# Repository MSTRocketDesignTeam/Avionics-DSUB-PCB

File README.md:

# Avionics-DSUB-PCB
Avionics DSUB board

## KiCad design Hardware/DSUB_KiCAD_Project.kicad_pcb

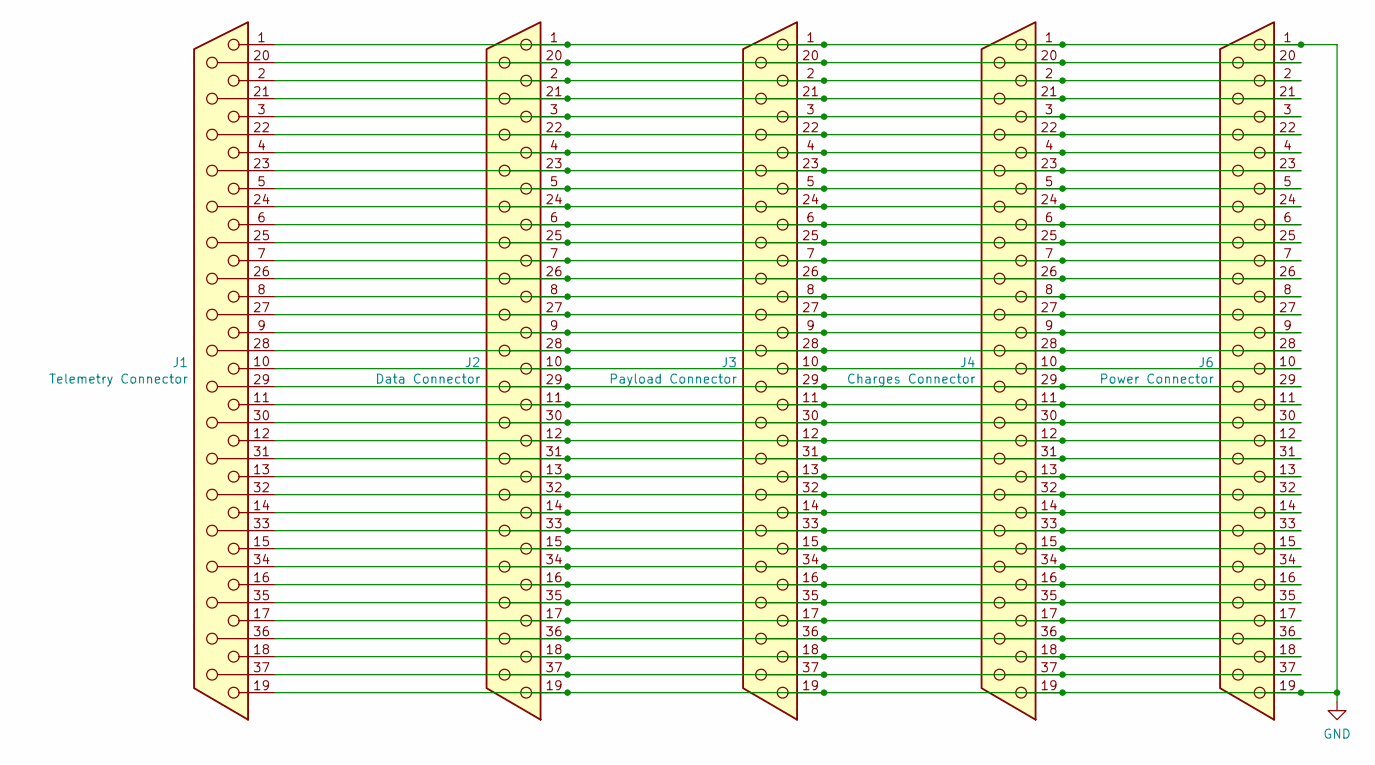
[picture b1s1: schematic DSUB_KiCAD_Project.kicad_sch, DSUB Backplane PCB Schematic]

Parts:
J1: Telemetry Connector; TE_1-747301-6
J2: Data Connector; TE_1-747301-6
J3: Payload Connector; TE_1-747301-6
J4: Charges Connector; TE_1-747301-6
J6: Power Connector; TE_1-747301-6

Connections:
GND: J1.1, J1.19, J2.1, J2.19, J3.1, J3.19, J4.1, J4.19, J6.1, J6.19
unnamed: J1.2, J2.2, J3.2, J4.2, J6.2
unnamed: J1.3, J2.3, J3.3, J4.3, J6.3
unnamed: J1.4, J2.4, J3.4, J4.4, J6.4
unnamed: J1.5, J2.5, J3.5, J4.5, J6.5
unnamed: J1.6, J2.6, J3.6, J4.6, J6.6
unnamed: J1.7, J2.7, J3.7, J4.7, J6.7
unnamed: J1.8, J2.8, J3.8, J4.8, J6.8
unnamed: J1.9, J2.9, J3.9, J4.9, J6.9
unnamed: J1.10, J2.10, J3.10, J4.10, J6.10
unnamed: J1.11, J2.11, J3.11, J4.11, J6.11
unnamed: J1.12, J2.12, J3.12, J4.12, J6.12
unnamed: J1.13, J2.13, J3.13, J4.13, J6.13
unnamed: J1.14, J2.14, J3.14, J4.14, J6.14
unnamed: J1.15, J2.15, J3.15, J4.15, J6.15
unnamed: J1.16, J2.16, J3.16, J4.16, J6.16
unnamed: J1.17, J2.17, J3.17, J4.17, J6.17
unnamed: J1.18, J2.18, J3.18, J4.18, J6.18
unnamed: J1.20, J2.20, J3.20, J4.20, J6.20
unnamed: J1.21, J2.21, J3.21, J4.21, J6.21
unnamed: J1.22, J2.22, J3.22, J4.22, J6.22
unnamed: J1.23, J2.23, J3.23, J4.23, J6.23
unnamed: J1.24, J2.24, J3.24, J4.24, J6.24
unnamed: J1.25, J2.25, J3.25, J4.25, J6.25
unnamed: J1.26, J2.26, J3.26, J4.26, J6.26
unnamed: J1.27, J2.27, J3.27, J4.27, J6.27
unnamed: J1.28, J2.28, J3.28, J4.28, J6.28
unnamed: J1.29, J2.29, J3.29, J4.29, J6.29
unnamed: J1.30, J2.30, J3.30, J4.30, J6.30
unnamed: J1.31, J2.31, J3.31, J4.31, J6.31
unnamed: J1.32, J2.32, J3.32, J4.32, J6.32
unnamed: J1.33, J2.33, J3.33, J4.33, J6.33
unnamed: J1.34, J2.34, J3.34, J4.34, J6.34
unnamed: J1.35, J2.35, J3.35, J4.35, J6.35
unnamed: J1.36, J2.36, J3.36, J4.36, J6.36
unnamed: J1.37, J2.37, J3.37, J4.37, J6.37

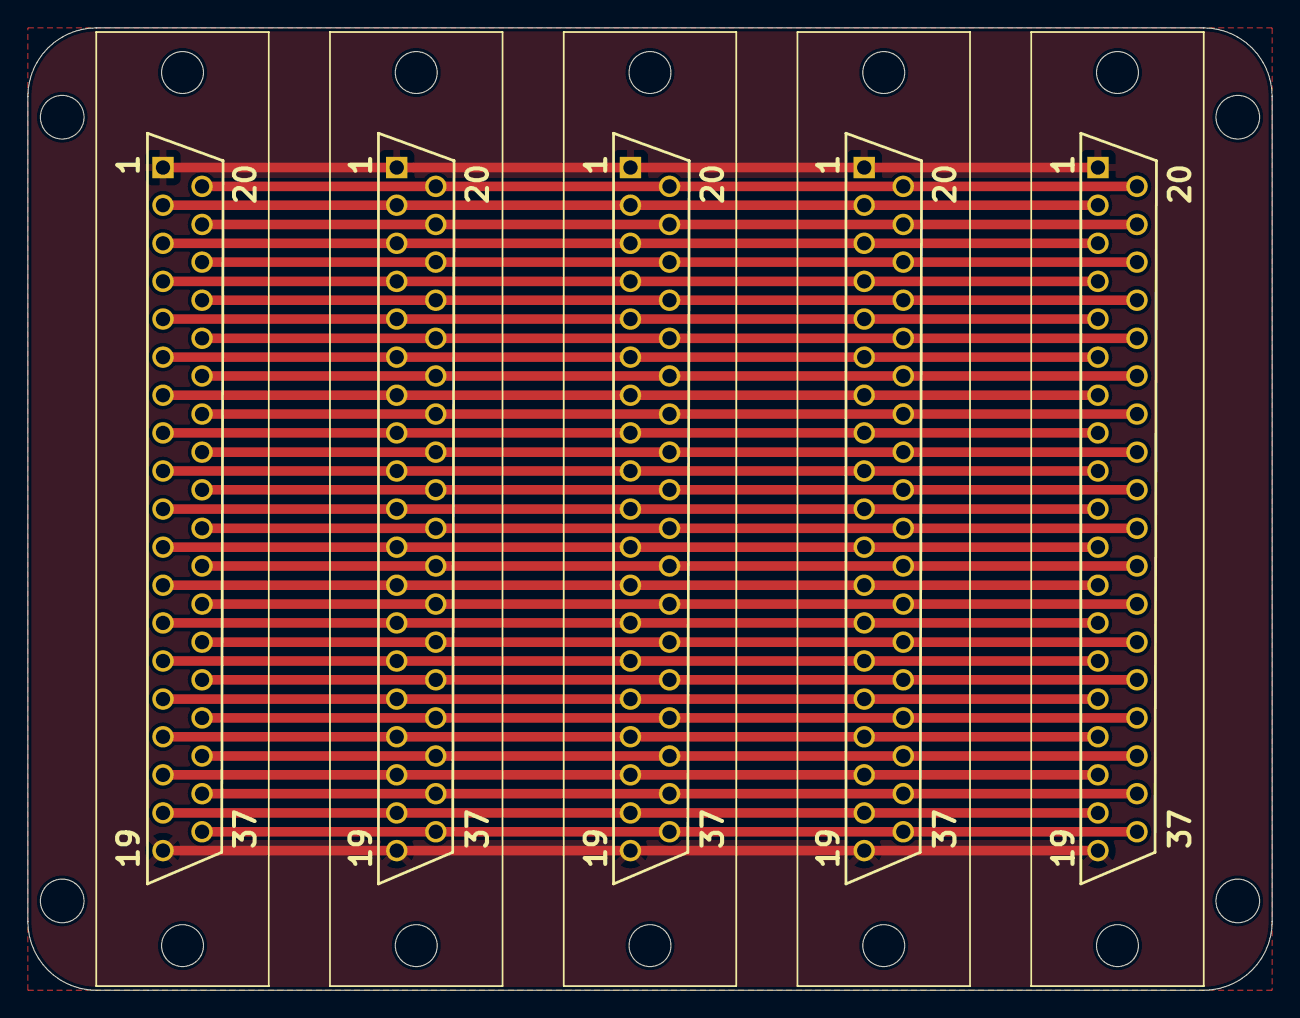
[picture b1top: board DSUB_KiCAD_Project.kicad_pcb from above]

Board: 2 copper layers, 90.5 x 70.0 mm, 5 parts (0 on the bottom side), 36 nets.

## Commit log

2021-12-02 Pcb made
    actually made the pcb
2021-12-03 Changed layout
    Layout was changed. Now we have planes for ground, 5v, and 3v3. hopefully current wont be an issue
2021-12-06 Create LICENSE
2021-12-06 Reformatted repo
2021-12-06 Corrected Schematic Hierarchical Pages
2021-12-06 added libraries
    added libraries from my global to this lib
2021-12-21 Added Component sheets
    Component sheets were added from the telemetry board to match across all boards
2022-01-18 rounded corners
    corners were rounded to 5mm
2022-01-18 Added 3D models to DSUB connectors
2022-01-18 Added more silk screen artwork
2022-01-18 Added GND vias and copper pours
2022-02-05 changed dimensions
    dimensions of the board was changed
2022-02-07 Added QR code to silkscreen
2022-02-12 Adjusted spacing between connectors
2022-02-14 Connectors face same way, adjusted spacing of misc connector
2022-02-14 Added silkscreen orientation labels
2022-02-28 Redesigned main schematic page, improved labeling on pcb, resized for 2U format
2022-02-28 Adjusted desub silk screen
2022-03-07 Added more silkscreen art
2022-03-18 Generated Gerb
    Gerb and drill files were generated
